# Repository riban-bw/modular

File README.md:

# riban modular

## Overview

Riban modular is an open source and (where practical) open hardware virtual modular synthesiser with physical control panels that fit the Eurorack physical format. See the [wiki](https://github.com/riban-bw/modular/wiki) for documentation.

There are hardware panels that represent each virtual module. The panels are plugged together via a daisy-chain ribbon cable which provides power and a CAN bus for inter-communication. Modules have rotary controls, switches, LEDs, etc. that mimic and control the virtual modules. A Raspberry Pi 5 forms the core, providing the audio processing and interfacing with the hardware panels. Panels are detected automatically when connected, creating a corresponding virtual module within the virtual modular system.

The system consists of a _Brain_ and panels. The Brain consists of a Raspberry Pi 5, STM32F103 microcontroller, CAN connector, audio interface and associated connectors, buttons, pots, etc. Panels consist of STM32F103 microcontroller, CAN connector and buttons, pots, etc.

Each panel is based on a STM32F103C8 microcontroller with a common firmware that supports various quantities and types of controls and indicators. Each panel has a type number that identifies what type of virtual module it represents.

Connect each module to a ribbon cable connector then power up the system. The core will communicate via CAN to detect which panels are installed, assign each panel an id then add a correspoding virtual module to its model.

## Usage

Hardware panels are required to interface with the firmware. See the [wiki](https://github.com/riban-bw/modular/wiki) for documentation.

## Building

There are two core elements to _riban modular_: Hardware panels (including the firmware that runs on them) and the core. Panel firmware is written in C++ for the STMicroelectronics STM32 range of ARM based microcontrollers. The core is written in C++ for the Raspberry Pi ARM based SBC. VSCode IDE is used by the developer with plugins including platformio, which provides the build platform for the STM32 firmware. VSCode is run on a development PC, connected via ssh to the target (Raspberry Pi) platform.

### Core

The core code runs on a Raspberry Pi (4 or later), running [DietPi](https://dietpi.com/) operating system. CMake is used as the build tool. We use some modules from Bogaudio so have a dependancy on their source code with a small patch to exclude the GUI code. To compile the code:

- Install dependencies, e.g. `sudo apt install build-essentials libjack-jackd2-dev git cmake nlohmann-json3-dev`
- Clone this repository, e.g. `git clone --recursive https://github.com/riban-bw/modular.git`
- Change to the directory, e.g. `cd modular/firmware/rmcore`
- Create a build directory, e.g. `mkdir build`
- Change to the build directory, e.g. `cd build`
- Create build files, e.g. `cmake ..`
- Build executable, e.g. `make`

An executable file called _rmcore_ is creaed in the build directory. This may be run with optional command line options, e.g. `rmcore -h` to show help / usage.

### Panels

Each panel has a platformio configuration. These build instructions are for platformio within vscode IDE. (You could just use platformio directly.) I have written up a [guide](https://github.com/riban-bw/blog/wiki/STM32--development-on-PlatformIO-in-VSCode-on-64-bi-ARM) to using platformio within vscode over ssh to a Raspberry Pi to develop STM32 code. Follow that guide to get a working build environment. There are sepearate platformio projects for each panel, defined by a _platformio.ini_ file in the panel's firmware directory.

- Within vscode, click on the platformio icon in the left toolbar.
- Click on "Open Folder" and open the panel directory.
- If this is the first time, platformio will download and install the STM32 toolkit which may take several minutes.
- Click on the tick icon in the bottom toolbar to build the project. First time build may take longer as it builds all the dependant libraries.

To switch panels, use vscode file menu, open folder... Each time a new panel project is opened for the first time, platformio takes some time to configure. (Even on subsequent switches, platformio can take some time to open a project.)

Be aware that rmcore is within the firmware directory but is not a panel firmware and should be built as described in the [above section](#core).

## CAN Protocol

Communication between the Brain and panels uses CAN two wire serial bus. CAN uses differential balanced cabling to provide robust, high speed communication over long distance. Detection of panels uses CAN extended frame format (to allow fewer frames during detection) whilst normal operation uses standad frame format (to allow shorter frames for realtime data). Each panel starts by advertising its 96-bit hardware UID (STM32 serial number). The Brain module detects new panels and negotiates a _panel id_ (1..63) for each. CAN uses a lowest-id-wins mechanism for bus arbitration which allows the Brain to negotiate each panel partaking in the detection process. The panel with the lowest UUID is assigned the next available panel id which then leaves the detection process and joins the pool of configured panels. The Brain iterates over all panels currently advertising their participation in the detection process.

Subsequent communication between the Brain and each panel is via CAN messages initiated by panels for sensor changes (switches, knobs, etc.) or the Brain for indications (LEDs, etc.). The message type is encoded in the CAN ID. Each panel uses CAN filters to only listen for messages from the Brain. Similarly the Brain listens for messages from panels. All CAN traffic occurs between STM32F103 based devices.

#### CAN Message Protocol

CAN message id is 11-bit (std) or 29-bit (ext) word.

Standard CAN format (11-bit id) is used for runtime realtime messages.

Extended CAN format (29-bit id) is used for configuration and firmware update.

#### CAN runtime realtime messages

Brain to panel (B→P) CAN ID: bit [0] = 0, bits [1:7] = panel id (1..63), bits [8:11] = opcode.

Panel to Brain (B←P) CAN ID: bits [0:7] = 0, bits [8:11] = opcode.

Brain to rmcore splits messages into whole bytes, i.e. CAN ID[1], opcode[1], data[8].

rmcore can send messages to the Brain by setting first byte to 0xFF or to a panel by setting first byte to panel (CAN) id.

CAN payload may have varying length (0..8 bytes) depending on message type.

Brain always listens for panel messages and may request values with appropriate commands. This is asynchronous.

Host (RPi) communicates with Brain via serial port, mostly using same CAN protocol, i.e. the Brain passes through the CAN messages. An exception is for panel detection which the Brain handles locally and passes a single message to the host after detecting each panel.

|B↔P| ID       | OpCode | Payload                                   | Purpose|
|---|----------|--------|-------------------------------------------|---------------------------|
|B→P| LED      | 0x01   | Index [0:7] Mode [0:7] RGB1 [0:23] RGB2 [0:23]   | Set LED type and mode. RGB colours are both optional |
|B←P| ADC      | 0x02   | PanelId [0:7] Index [0:7] Value [0:15]           | ADC value|
|B←P| SW       | 0x03   | PanelId [0:7] Index[0:7] EventType [0:7]         | See below for event types |
|B←P| ENC      | 0x04   | PanelId [0:7] Index [0:7] Value [0:7]            | Encoder value +/- |
|B←P| PNL_DUMP | 0xF1   | PanelId [0:7]                                    | Request panel to send its parameter values |
|B←P| ALIVE    | 0x0E   |                                                  | Sent periodically if no other data sent to support watchdog |
|B→P| RESET    | 0x0F   |                                                  | Request panel to reset to detection mode |
|B←H| NUM_PNL  | 0x01   |                                                  | Request quantity of detected panels
|B←H| PNL_INFO | 0x01   |                                                  | Request type of all panels
|B→H| PNL_INFO | 0x01   | PanelId [0:5] Type [0:31] UUID [0:95] Ver [0:31] | Panel type (sent when new panel detected or PNL_INFO requested)
|B→H| PNL_REMOVED | 0x02 | PanelId [0:5] UUID [0:95]                       |
|B←H| PNL_RUN  | 0x03 |                                                    | Request all panels go to run mode

##### LED Modes
|Value|Mode|
|---|---|
|0x00|Off|
|0x01|Colour 1 on|
|0x02|Colour 2 on|
|0x03|Flash colour 1 / colour 2|
|0x04|Fast flash colour 1 / colour 2|
|0x05|Pulse colour 1 / colour 2|
|0x06|Fast pulse colour 1 / colour 2|

##### Switch States
|Value|State|
|---|---|
|0x00|Release|Sent when a button is released less than 0.5s after it was pressed (short press) or after a long press has triggered|
|0x01|Press|Always sent when a button is pressed|
|0x02|Bold|Sent when a button is released more than 0.5s after it was pressed but a long press has not triggered|
|0x03|Long|Sent when a button is held for longer than 1.5s|

#### Panel Detection

Panels advertise themselves with a CAN message which the Brain detects and starts a negotation. Detection messages use extended CAN ID which is 29-bits long (compared with standard frames used for realtime messages which are 11-bits). Each panel advertises itself by encoding its 96-bit UUID in the CAN ID of 4 consecutive messages. Each message is acknowledged by the Brain, indicating which panel UUID are accepted. Only panels that match that segment of the UUID continue with the negotiation. Eventually only one panel remains and is assigned a panel ID. Finally the panel indicates it has accepted the panel, sending its type and version. This allows the Brain to build a table of panel UUID, panel ID and panel type so that the core can create the appropriate virtual modules. It also allows the Brain to know whether a panel is running old firmware, allowing firmware update. The table is used to ensure that existing panels that restart, e.g. after a firmware update get the same panel ID.

|B⬌P| ID        | ID                | Payload                    | Purpose |
|----|-----------|-------------------|----------------------------|---------------------------|
|B←P| DETECT_1  | 0x1F<UUID[0:23]>  |                            | Notify Brain that panel is added to bus but not initialised |
|B→P| DETECT_1  | 0x1F000000        | UUID[0:23]                 | Brain acknowledges lowest UUID panels |
|B←P| DETECT_2  | 0x1E<UUID[24:47]> |                            | Panel requests detect stage 2 |
|B→P| DETECT_2  | 0x1E000000        | UUID[24:47]                | Brain acknowledges lowest UUID panels |
|B←P| DETECT_3  | 0x1D<UUID[48:71]> |                            | Panel requests detect stage 3 |
|B→P| DETECT_3  | 0x1D000000        | UUID[48:71]                | Brain acknowledges lowest UUID panels |
|B←P| DETECT_4  | 0x1C<UUID[71:95]> |                            | Panel requests detect stage 4 |
|B→P| DETECT_4  | 0x1C000000        | UUID[72:95] PanelID[0:7]   | Brain acknowledges UUID of only remaining panel |
|B←P| ACK_ID    | 0x1B0000<PanelId> | Type [0:31] Version [0:31] | Panel acknowledges ID and informs Brain of its version & type |

#### Broadcast messages and firmware update

The CAN ID 0x000 is used to broadcast messages to all panels. This is the highest priority CAN ID (lowest value wins all bus conflict negotiation) and is used for low latency messaging (e.g. synchronisation) and firmware update. The first byte of a broadcast payload data is the opcode for a command. All broadcast messages use standard (11-bit) CAN format.

Broadcast messages
|Dir | ID        | ID         | Payload                           | Purpose
|----|-----------|------------|-----------------------------------|---------------------------------------------------------
|B→P| BROADCAST | 0x00000000 | OPCODE[0:7]                       | Broadcast from Brain payload contains opcode (see below) |
|B→P| BROADCAST | 0x00000000 | 0x01 UUID[0:23]                   | Start detection - all panels should join detection without software reset |
|B→P| BROADCAST | 0x00000000 | 0x02 PanelType [0:23] Ver [0:31]  | Start firmware update |
|B→P| BROADCAST | 0x00000000 | 0x03 Checksum [0:31]              | End firmware update |
|B→P| FIRMWARE  | 0x01000000 | Firmware Block [0:63]             | Firmware update data block |
|B→P| BROADCAST | 0x00000000 | 0xFF                              | Full reset - all panels should perform software reset |

Firmware is started with the broadcast message (CAN ID=0x000) with opcode 0x02. The panel type and firmware version are sent in this message. Any panel of this type with an older firmware will join the firmware update. Subsequent firmware update messages use the CAN ID 0x400 (msb set) with 8 bytes of firmware data. Panels configure a CAN filter to listen to this address during firmware update only. Upon completion of firmware update the Brain sends broadcast message with opcode 0x03 and a 32-bit checksum of the firmware data. The Brain ends its firmware update. Panels validate the checksum then apply the new firmware, restart and advertise as new panels.

#### Watchdog

Each panel periodically sends an ALIVE message if no other message has been sent in the previous 1.5s. If the Brain has not received any message from a panel for longer than 2s it assumes the panel has been removed  from the bus and removes its entry from the panel table. This triggers removal of the corresponding virtual module.

## Configuration

Configuration is stored in config.json which is loaded before command line parameters are parsed, so command line parameters take precedent.

Global settings are defined in the "global" object.

```
{
    "global": { # Global settings
        "polyphony": 1 # Quantity of concurrent voices (1..16)
    }
}
```

Each panel is defined in "panel" object.

```
{
    "panels" : { # Object of panel types
        "1": { # Object of panel configuration indexed by panel type id
            "module": "vco", # Name of the module type this panel controls
            "buttons": [ # List of buttons, indexed by physical button number
                [0, # Button function (input, poly input, output, poly output, param)
                0], # Index of the parameter or input/output
                # .. more button configs
            ],
            "leds": [ # List of LEDs, indexed by physical LED number
                [0, # LED function  (input, poly input, output, poly output, param)
                0], # Index of parameter or input/output
                # ... more LEDs
            ],
            "adcs": [ # List of parameters, indexed by physical ADC number
                0, # Parameter index
                # ... more ADCs
            ]
            "encs": { # List of parameters, indexed by physical PEC11 encoder number
                0, # Parameter index
                # ... more encoders
            }
        }, # ... More panel types
    }
}
```

panel_types.h defines mapping of panel types to module types and defines the STM32F103 pins used for sensors (controls) on each panel. 

## License

_riban modular_ is free and open source software, avaialble for distibution, use and modification by all. It has three open source licences, each applied to different parts of the code. Each source code file (including headers) contain a copyright notice describing which license applies to that part of the code. If a file is missing this banner, LGPL v3 is applied.

### LGPL V3
LGPL v3 is used for the core software and some plugins. This protects the core application whilst allowing non-open source plugins to be hosted by exercising dynamic linking with runtime loading (plugin exception). The text of the LGPL v3 license is distributed with the source code within the file called, lgpl-3.0.txt and may also be obtained from https://www.gnu.org/licenses/lgpl-3.0.en.html.

### GPL V3
To support plugins derived from GPL licensed code, some plugins have been licenced using GPL v3. These plugins continue to be fully copy-left protected whilst also able to be loaded into the core application using dynamic linking with runtime loading (plugin exception). The text of the GPL v3 license is distributed with the source code within the file called, gpl-3.0.txt and may also be obtained from https://www.gnu.org/licenses/gpl-3.0.en.html.

### MIT
To encourage third party plugin developement, there is a plugin template released under MIT license. This permits the use of the template as the basis of new plugins with the option for the author to release the derived work under any other license. We encourage use of LGPL for plugins where an open source license is required or preferred.

### Guidance and advice for plugin creators

If you are creating plugins to run within _riban modular_, you may use the `template.h` and `template.cpp` files as the boiler plate code. These files are published under the MIT license, specifically to allow and encourage developers to create new plugins without restricitve licensing constraints. You may create a new plugin and use the _riban modular_ cmake based build system to create the shared library. You may release this under a license that best suits your use case. You must attribute riban ltd as the author of the original template code, as described in the template source code.

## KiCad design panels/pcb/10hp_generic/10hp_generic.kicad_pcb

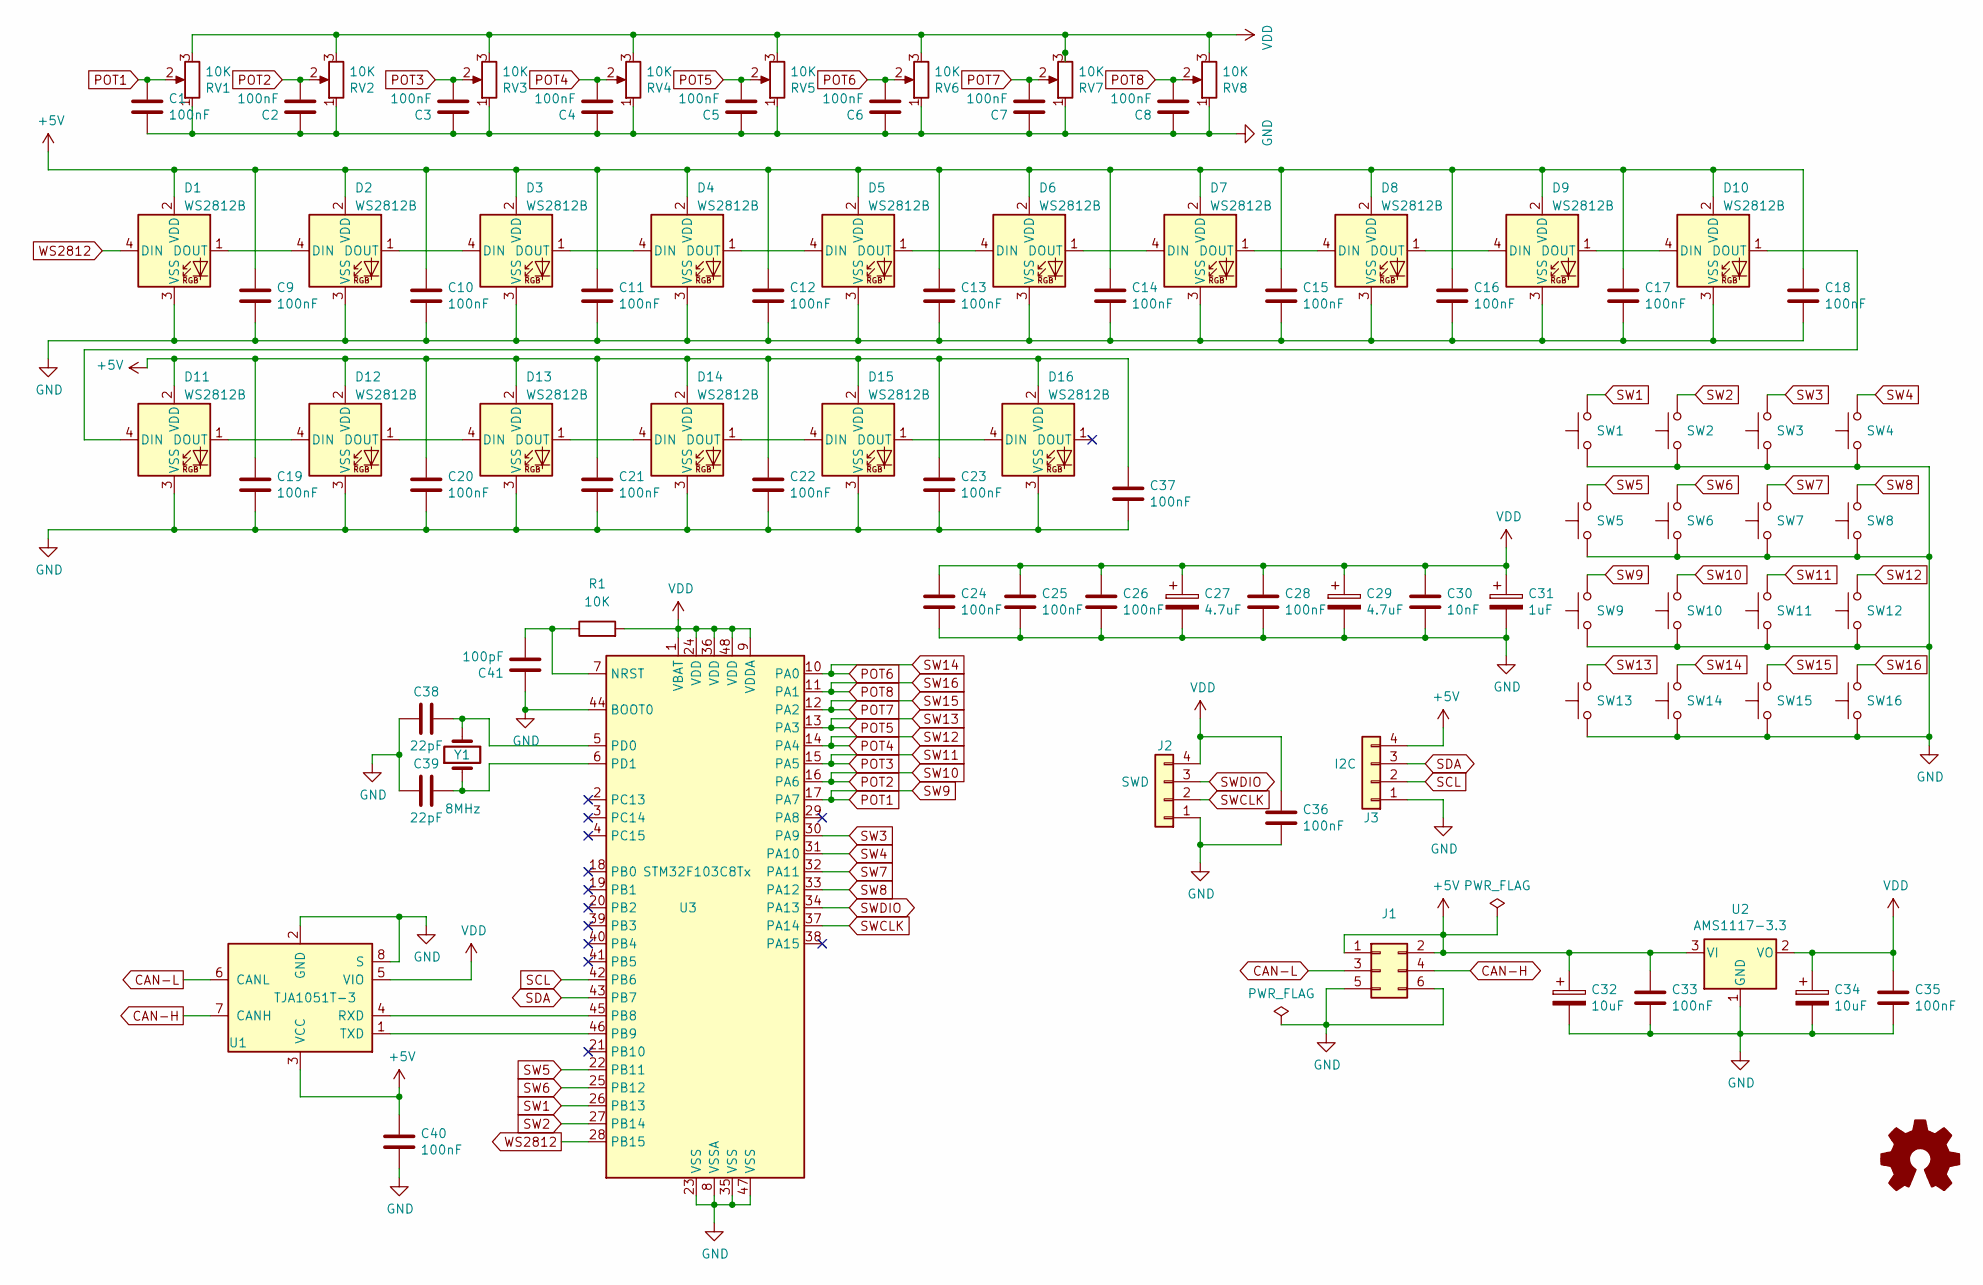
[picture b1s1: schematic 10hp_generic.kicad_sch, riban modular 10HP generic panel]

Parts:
C1, C2, C3, C4, C5, C6, C7, C8, C9, C10, C11, C12, C13, C14, C15, C16, C17, C18, C19, C20, C21, C22, C24, C25, C26, C28, C33, C35, C36, C40: 100nF; C_0402_1005Metric; LCSC C1525
C23, C37: 100nF; C_0603_1608Metric; LCSC C14663
C27, C29: 4.7uF; C_0805_2012Metric; LCSC C1779
C30: 10nF; C_0402_1005Metric; LCSC C15195
C31: 1uF; C_0402_1005Metric; LCSC C52923
C32, C34: 10uF; C_0805_2012Metric; LCSC C15850
C38, C39: 22pF; C_0603_1608Metric; LCSC C326840
C41: 100pF; C_0402_1005Metric; LCSC C1546
D1, D2, D3, D4, D5, D6, D7, D8, D9, D10, D11, D12, D13, D14, D15, D16: WS2812B; LED_XL-1615RGBC-WS2812B; LCSC C5349954
J1: CAN_PWR; IDC-Header_2x03_P2.54mm_Vertical
J2: SWD; PinHeader_1x04_P2.54mm_Vertical
J3: I2C; PinHeader_1x04_P2.54mm_Vertical
R1: 10K; R_0402_1005Metric
RV1, RV2, RV3, RV4, RV5, RV6, RV7, RV8: 10K; Potentiometer_9mm_Vertical; LCSC C470336
SW1, SW2, SW3, SW4, SW5, SW6, SW7, SW8, SW9, SW10, SW11, SW12, SW13, SW14, SW15, SW16: SW_Push; SW_PUSH_6mm_H4.3mm; LCSC C5260475
U1: TJA1051T-3; SOIC-8_3.9x4.9mm_P1.27mm; LCSC C38695
U2: AMS1117-3.3; SOT-223; LCSC C6186
U3: STM32F103C8Tx; LQFP-48_7x7mm_P0.5mm; LCSC C8734
Y1: 8MHz; HC-49S; LCSC C12674

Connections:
+5V: C9.1, C10.1, C11.1, C12.1, C13.1, C14.1, C15.1, C16.1, C17.1, C18.1, C19.1, C20.1, C21.1, C22.1, C23.1, C32.1, C33.1, C37.1, C40.1, D1.2 (VDD), D2.2 (VDD), D3.2 (VDD), D4.2 (VDD), D5.2 (VDD), D6.2 (VDD), D7.2 (VDD), D8.2 (VDD), D9.2 (VDD), D10.2 (VDD), D11.2 (VDD), D12.2 (VDD), D13.2 (VDD), D14.2 (VDD), D15.2 (VDD), D16.2 (VDD), J1.1, J1.2, J3.4, U1.3 (VCC), U2.3 (VI)
CAN-H: J1.4, U1.7 (CANH)
CAN-L: J1.3, U1.6 (CANL)
GND: C1.2, C2.1, C3.1, C4.1, C5.1, C6.1, C7.1, C8.1, C9.2, C10.2, C11.2, C12.2, C13.2, C14.2, C15.2, C16.2, C17.2, C18.2, C19.2, C20.2, C21.2, C22.2, C23.2, C24.2, C25.2, C26.2, C27.2, C28.2, C29.2, C30.2, C31.2, C32.2, C33.2, C34.2, C35.2, C36.2, C37.2, C38.1, C39.1, C40.2, C41.1, D1.3 (VSS), D2.3 (VSS), D3.3 (VSS), D4.3 (VSS), D5.3 (VSS), D6.3 (VSS), D7.3 (VSS), D8.3 (VSS), D9.3 (VSS), D10.3 (VSS), D11.3 (VSS), D12.3 (VSS), D13.3 (VSS), D14.3 (VSS), D15.3 (VSS), D16.3 (VSS), J1.5, J1.6, J2.1, J3.1, RV1.1, RV2.1, RV3.1, RV4.1, RV5.1, RV6.1, RV7.1, RV8.1, SW1.1, SW2.1, SW3.1, SW4.1, SW5.1, SW6.1, SW7.1, SW8.1, SW9.1, SW10.1, SW11.1, SW12.1, SW13.1, SW14.1, SW15.1, SW16.1, U1.2 (GND), U1.8 (S), U2.1 (GND), U3.8 (VSSA), U3.23 (VSS), U3.35 (VSS), U3.44 (BOOT0), U3.47 (VSS)
unnamed: D1.1 (DOUT), D2.4 (DIN)
unnamed: D2.1 (DOUT), D3.4 (DIN)
unnamed: D3.1 (DOUT), D4.4 (DIN)
unnamed: D4.1 (DOUT), D5.4 (DIN)
unnamed: D5.1 (DOUT), D6.4 (DIN)
unnamed: D6.1 (DOUT), D7.4 (DIN)
unnamed: D7.1 (DOUT), D8.4 (DIN)
unnamed: D8.1 (DOUT), D9.4 (DIN)
unnamed: D9.1 (DOUT), D10.4 (DIN)
unnamed: D10.1 (DOUT), D11.4 (DIN)
unnamed: D11.1 (DOUT), D12.4 (DIN)
unnamed: D12.1 (DOUT), D13.4 (DIN)
unnamed: D13.1 (DOUT), D14.4 (DIN)
unnamed: D14.1 (DOUT), D15.4 (DIN)
unnamed: D15.1 (DOUT), D16.4 (DIN)
unnamed: U1.4 (RXD), U3.45 (PB8)
unnamed: U1.1 (TXD), U3.46 (PB9)
unnamed: C41.2, R1.1, U3.7 (NRST)
unnamed: C38.2, U3.5 (PD0), Y1.2
unnamed: C39.2, U3.6 (PD1), Y1.1
POT1: C1.1, RV1.2, SW9.2, U3.17 (PA7)
POT2: C2.2, RV2.2, SW10.2, U3.16 (PA6)
POT3: C3.2, RV3.2, SW11.2, U3.15 (PA5)
POT4: C4.2, RV4.2, SW12.2, U3.14 (PA4)
POT5: C5.2, RV5.2, SW13.2, U3.13 (PA3)
POT6: C6.2, RV6.2, SW14.2, U3.10 (PA0)
POT7: C7.2, RV7.2, SW15.2, U3.12 (PA2)
POT8: C8.2, RV8.2, SW16.2, U3.11 (PA1)
SCL: J3.2, U3.42 (PB6)
SDA: J3.3, U3.43 (PB7)
SW1: SW1.2, U3.26 (PB13)
SW2: SW2.2, U3.27 (PB14)
SW3: SW3.2, U3.30 (PA9)
SW4: SW4.2, U3.31 (PA10)
SW5: SW5.2, U3.22 (PB11)
SW6: SW6.2, U3.25 (PB12)
SW7: SW7.2, U3.32 (PA11)
SW8: SW8.2, U3.33 (PA12)
SWCLK: J2.2, U3.37 (PA14)
SWDIO: J2.3, U3.34 (PA13)
VDD: C24.1, C25.1, C26.1, C27.1, C28.1, C29.1, C30.1, C31.1, C34.1, C35.1, C36.1, J2.4, R1.2, RV1.3, RV2.3, RV3.3, RV4.3, RV5.3, RV6.3, RV7.3, RV8.3, U1.5 (VIO), U2.2 (VO), U3.1 (VBAT), U3.9 (VDDA), U3.24 (VDD), U3.36 (VDD), U3.48 (VDD)
WS2812: D1.4 (DIN), U3.28 (PB15)

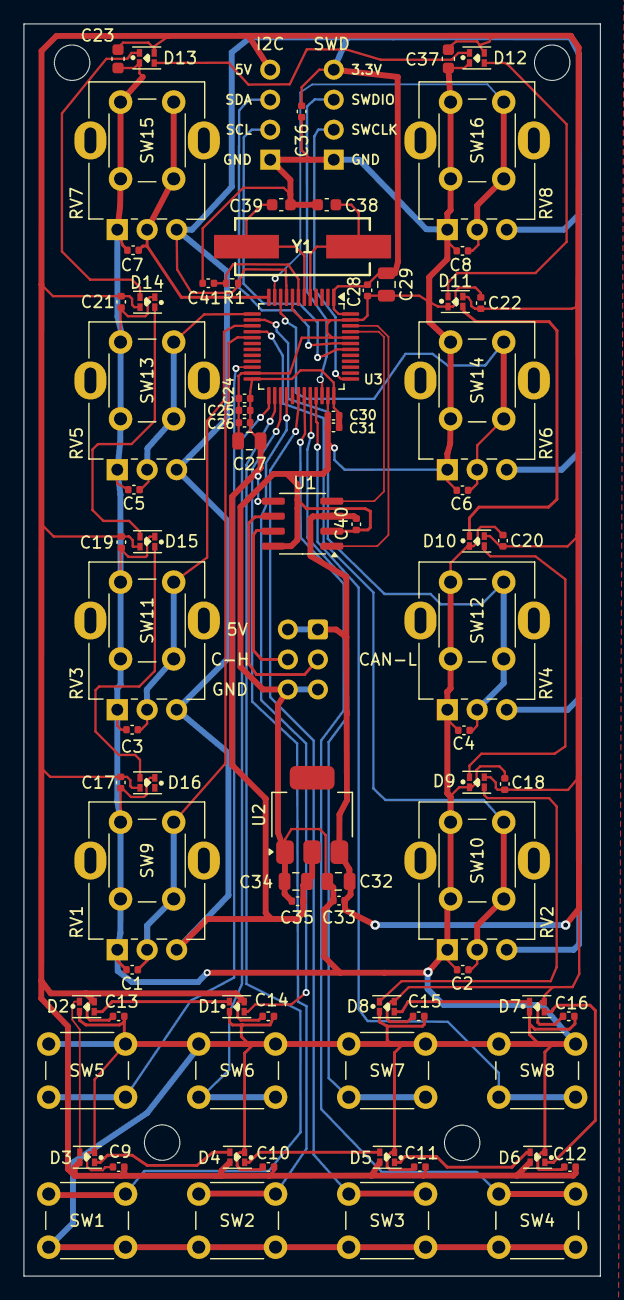
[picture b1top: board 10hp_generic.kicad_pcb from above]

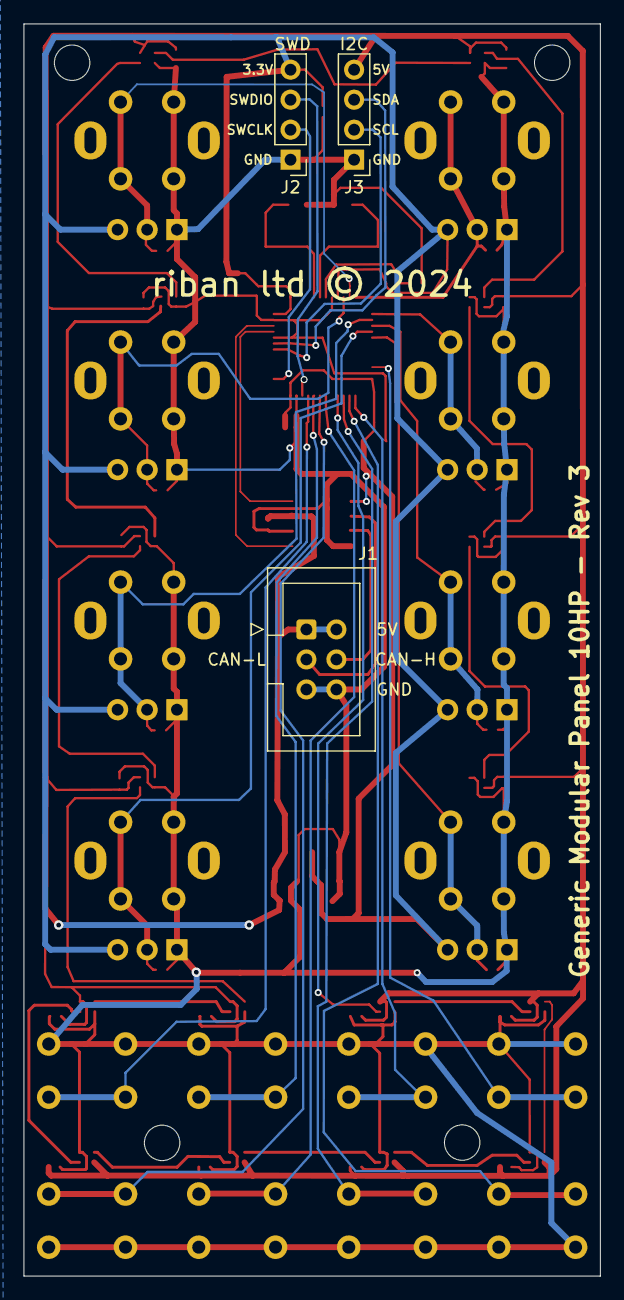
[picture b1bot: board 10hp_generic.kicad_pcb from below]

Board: 2 copper layers, 48.8 x 106.0 mm, 89 parts (3 on the bottom side), 46 nets.

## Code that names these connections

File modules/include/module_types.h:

/* riban modular
  
  Copyright 2023 riban ltd <info@riban.co.uk>

  This file is part of riban modular.
  riban modular is free software: you can redistribute it and/or modify it under the terms of the GNU General Public License as published by the Free Software Foundation, either version 3 of the License, or (at your option) any later version.
  riban modular is distributed in the hope that it will be useful, but WITHOUT ANY WARRANTY; without even the implied warranty of MERCHANTABILITY or FITNESS FOR A PARTICULAR PURPOSE. See the GNU General Public License for more details.
  You should have received a copy of the GNU General Public License along with riban modular. If not, see <https://www.gnu.org/licenses/>.

  Defines each module configuration based on preprocessor directive MODULE_TYPE which should be defined in build system.
*/

#ifndef MODULE_TYPE
#error Module type not defined
#endif //MODULE_TYPE

/* Available GPI (STM32F103 Bluepill dev board)
PORT|ADC|PWM|COMMS|Note
-----------------------
PA0 | X | X |     |
PA1 | X | X |     |
PA2 | X | X |     |
PA3 | X | X |     |
PA4 | X |   |     |
PA5 | X |   |     |
PA6 | X | X |     |
PA7 | X | X |     |
PA8 |   | X |     |
PA9 |   | X |     |
PA10|   | X |     |
PA11|   |   |USB- |Only for debug
PA12|   |   |USB+ |Only for debug
PA13|   |   |     |End header programming pin
PA14|   |   |     |End header programming pin
PA15|   |   |     |
PB0 | X | X |     |
PB1 | X | X |     |
PB2 |   |   |     |Top header boot pin
PB3 |   |   |     |
PB4 |   |   |     |
PB5 |   |   |     |
PB6 |   | X |     |
PB7 |   | X |     |
PB8 |   | X |     |
PB9 |   | X |     |
PB10|   |   |SCL  |I2C
PB11|   |   |SDA  |I2C
PB12|   |   |     |
PB13|   |   |     |
PB14|   |   |     |
PB15|   |   |MOSI2|WS2812 control
PC13|   |   |LED  |
PC14|   |   |     |Next module reset
PC15|   |   |     |
*/

#define ADC_PINS {PA0, PA1, PA2, PA3, PA4, PA5, PA6, PA7, PB0, PB1}
#define PWM_PINS {PA0, PA1, PA2, PA3, PA6, PA7, PA8, PA9, PA10, PB0, PB1, PB6, PB7, PB8, PB9}
#define GPI_PINS {PB0, PB1, PB3, PB4, PB5, PB6, PB7, PB8, PB9, PB12, PB13, PB14, PC15, PA15}
#define SCL_PIN PB10
#define SDA_PIN PB11
#define MOSI_PIN PB15 //WS2812 LED data
#define RESET_PIN PC14

#if MODULE_TYPE==1
// Host Audio
//!@todo May want a core module that provides audio & MIDI
#define ADCS 1
#define SWITCHES 4
#define WSLEDS 4
#endif // MODULE_TYPE 1

#if MODULE_TYPE==11
// VCV Fundamental VCO
#define ADCS 4
#define SWITCHES 10
#define WSLEDS 10
#endif // MODULE_TYPE 11

#if MODULE_TYPE==12
// VCV Fundamental VCF
#define ADCS 6
#define SWITCHES 6
#define WSLEDS 6
#endif // MODULE_TYPE 12

#if MODULE_TYPE==13
// VCV Fundamental VCA
#define ADCS 1
#define SWITCHES 3
#define WSLEDS 3
//!@todo Indicate level, e.g. +24 (WS)LEDs
#endif // MODULE_TYPE 13

#if MODULE_TYPE==14
// VCV Fundamental ADSR
#define ADCS 8
#define SWITCHES 8
#define WSLEDS 8
#endif // MODULE_TYPE 14

#if MODULE_TYPE==15
// VCV Fundamental VCA-2
#define ADCS 2
#define SWITCHES 8
#define WSLEDS 8
#endif // MODULE_TYPE 15

#if MODULE_TYPE==16
// VCV Fundamental VCA MIX
#define ADCS 10
#define SWITCHES 14
#define WSLEDS 14
#endif // MODULE_TYPE 16

#if MODULE_TYPE==17
// VCV Fundamental MERGE
#define ADCS 0
#define SWITCHES 17
#define WSLEDS 17
#endif // MODULE_TYPE 17

#if MODULE_TYPE==18
// VCV Fundamental RANDOM
#define ADCS 8
#define SWITCHES 12
#define WSLEDS 12
#endif // MODULE_TYPE 18

#if MODULE_TYPE==19
// VCV Fundamental NOIZ
#define ADCS 0
#define SWITCHES 7
#define WSLEDS 7
#endif // MODULE_TYPE 19

#if MODULE_TYPE==20
// VCV Fundamental M/S
#define ADCS 2
#define SWITCHES 10
#define WSLEDS 10
#endif // MODULE_TYPE 20

#if MODULE_TYPE==21
// VCV Fundamental SPLIT
#define ADCS 0
#define SWITCHES 17
#define WSLEDS 17
#endif // MODULE_TYPE 21

#if MODULE_TYPE==22
// VCV Fundamental 4-1
#define ADCS 0
#define SWITCHES 7
#define WSLEDS 7
#define LEDS 3
#endif // MODULE_TYPE 22

#if MODULE_TYPE==23
// VCV Fundamental 1-4
#define ADCS 0
#define SWITCHES 7
#define WSLEDS 7
#define LEDS 3
#endif // MODULE_TYPE 23

#if MODULE_TYPE==24
// VCV Fundamental SEQ3
#define ADCS 28
#define SWITCHES 31
#define WSLEDS 31
#endif // MODULE_TYPE 24

#if MODULE_TYPE==25
// VCV Fundamental PULSES
#define ADCS 0
#define SWITCHES 30
#define WSLEDS 30
#endif // MODULE_TYPE 25

#if MODULE_TYPE==26
// VCV Fundamental MUTES
#define ADCS 0
#define SWITCHES 30
#define WSLEDS 30
#endif // MODULE_TYPE 26

#if MODULE_TYPE==27
// VCV Fundamental 8VERT
#define ADCS 8
#define SWITCHES 16
#define WSLEDS 16
#endif // MODULE_TYPE 27

#if MODULE_TYPE==28
// VCV Fundamental MIX
#define ADCS 1
#define SWITCHES 7
#define WSLEDS 7
#endif // MODULE_TYPE 28

#if MODULE_TYPE==29
// VCV Fundamental LFO
#define ADCS 4
#define SWITCHES 10
#define WSLEDS 10
#endif // MODULE_TYPE 29

#if MODULE_TYPE==30
// VCV Fundamental OCT
#define ADCS 1
#define SWITCHES 3
#define WSLEDS 3
#endif // MODULE_TYPE 30

#if MODULE_TYPE==31
// VCV Fundamental WT VCO
#define ADCS 4
#define SWITCHES 7
#define WSLEDS 7
//!@todo Load, select and indicate wavetable / waveform
#define DISPLAY 1
#endif // MODULE_TYPE 31

#if MODULE_TYPE==32
// VCV Fundamental SUM
#define ADCS 1
#define SWITCHES 2
#define WSLEDS 2
#define LEDS 6
#endif // MODULE_TYPE 32

#if MODULE_TYPE==33
// VCV Fundamental QNT
#define ADCS 1
#define SWITCHES 14
#define WSLEDS 14
//!@todo Implement keyboard
#endif // MODULE_TYPE 33

#if MODULE_TYPE==34
// VCV Fundamental WT LFO
#define ADCS 4
#define SWITCHES 7
#define WSLEDS 7
//!@todo Load, select and indicate wavetable / waveform
#endif // MODULE_TYPE 33

#if MODULE_TYPE==35
// VCV Fundamental DELAY
#define ADCS 8
#define SWITCHES 8
#define WSLEDS 8
#endif // MODULE_TYPE 35

/*===========================================================================
    Define macros not specified (used) by module

    DO NOT CHANGE THIS - add new modules above
*/

#ifndef SWITCHES
#define SWITCHES 0 // Defines quantity of switch pins
#endif //SWITCHES
#ifndef ADCS
#define ADCS 0 // Defines quantity of analogue inputs like potentiometers
#endif //ADCS
#ifndef LEDS
#define LEDS 0 // Defines quanity of simple LED outputs
#endif //LEDS
#ifndef WSLEDS
#define WSLEDS 0  // Defines quantity of WS2812 LEDs
#endif //WSLEDS

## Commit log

2023-04-03 Adds module firmware source
2023-04-05 Adds Python host
2023-04-05 Port code to PlatformIO/VSCode
2023-08-05 Adds OSC interface to Cardinal
2023-08-07 Adds OSC interface to (riban modified) Cardinal. Updates README.
2023-08-07 Fix typo in README
2023-08-13 Implement I2C interface. Add module configuration. Add WS2812 LED control.
2023-08-13 Fixes I2C issues
2023-08-14 Add I2C command to turn LED on with colour 2
2023-08-14 Add ability to change LED colour and mode separately
2023-08-20 Add config for VCV modules. Reallocate GPI pins. Add function to temporarily turn all LEDs off. Synchronise pulse and flash across module (still need to sync between modules). Fast pulse LEDs on rese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
2023-08-22 Add function to get changed value from module. Use 16-bit values instead of 32-bit. Include address of data in return message. Reduce I2C responses from 4 to 3 bytes. Add more info to serial debug in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
2023-08-22 Fix setting i2c address
2023-08-25 Started integration with rack
2023-08-26 Initial version of host code (modular.py)
2023-08-27 Use min/max for rack parameter scaling / offset. Implement routing logic including LED feedback. Reduce panel reset LED flash duration.
2023-09-01 Do not use reset - use run GPI
2023-09-01 Add 10HP PCB
2023-09-08 PCB for generic 10hp panel (r1) including front panel for bogaudio VCO
2023-09-08 Fixes PCB footprint for C27 & C29
2023-09-08 Fixes some component values
2023-09-09 R2 of generic PCB using different components
2023-09-15 Add 1-wire module detection
2023-09-16 Adds brain front panel
2023-09-28 Fix host comms.
2023-09-28 Fixes and ehancements
2023-09-28 Adds VCF module. Connect jack audio at startup.
2023-09-28 Add Bogaudio LVCF
2023-10-02 Adds universal panel
2023-10-06 Refactor to use module id instead of I2C address - wip!
2023-10-09 Initial attempt at adding a website to gitlab pages
2023-10-09 Add website builder script
2023-10-09 Try to make website builder script work
2023-10-09 More website stuff
2023-10-13 Improvements to generic 10HP board layout. Implement exponential moving average filter on ADC reads.
2023-10-13 Fixes VCO PWM/FM input swap. Fixes errors in refactor of multiple module hosting panels.
2023-11-06 Typo in panel.cpp
2023-11-11 Adds STM32F1 generic panel firmware using CAN bus - wip
2023-11-11 Fix panel type not being set
2023-12-22 Changes made on laptop that needs to be wiped
2024-02-01 Add CAN based firmware
2024-02-01 Implement WS2812 LED control
2024-02-01 Adjust LED flash/pulse rates
2024-02-01 Rationalise CAN messaging. Add switches.
2024-02-02 Use 10kbps CAN for testing - avoid unreliable CAN interferring with tests. Handle existing panels resetting / connecting to brain. (Reuse existing records.) Implement I2C to CAN message sending. Fix 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
2024-02-06 Fixes CAN based detection
2024-02-06 Adds ADC and python test script
2024-02-06 Tuning EMA filter
2024-02-26 Rev 3 Firmware
    Replace I2C interface with CAN.
    Change from STM32F0 to STM32F1 processor.
    Panel detection now done on CAN so can remove 2 detect wires.
2024-02-26 Adds 10HP Generic PCB
2024-02-26 Adds front panels
2024-02-29 PCB design for generic r3 (wip)
2024-03-05 Rev 3 PCB routing done
2024-03-07 Rev 3 boards complete - probably
2024-03-08 R3 PCB and front panel
2024-03-14 Adds boilerplate for core host application
2024-04-05 Updated PCB fixing issues with r3: Reversed power pins on U1. Increase size of potentiometer anchors holes. Enable external high speed clock. Enable all LEDs, switches and pots.
2024-04-05 Fixes for firmware
2024-04-08 Replace I2C with USART
2024-04-09 Create brain STM32F103 firmware
2024-04-10 Implementing USART interface in host application - wip
2024-04-10 1Mbps usart mostly working
2024-04-11 Some optimisation and removal of stale code
2024-04-11 Fixes to generic 10hp schematic and PCB
2024-04-11 Tidy files
2024-04-11 Removes pages publish script (no longer using for webpage)
2024-09-23 Adds initial core code
2024-09-23 Work on core
2024-09-23 Add version and start of rack stub
2025-04-24 Adds oscillator.
2025-04-24 Remove oscillator code from main. Use static header file for wavetable data. Add application to build wavetable data. Add square wave oscillator with PWM. Add code documentation. Fix copyright notice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
2025-04-25 Switch from alsa to jack. Implement plugin mechanism for modules.
2025-04-25 Improve and simplify configuration of plugins. Add one-pole filtering of oscillator frequency control to reduce zipping.
2025-04-25 Adds amplifer module
2025-04-26 Move info into module constructor
2025-04-26 Add MIDI. Add filter (not working properly yet). Use CV input to oscillator to set frequency based on 1v/oct. Fix segfault when setting param value.
2025-04-27 Add polyphony (max 16, set by command line parameter -p)
2025-04-28 Use jack samplerate. Implement envelope. Implement polyphony. Add oscillator waveform morph control.
2025-04-28 Adds MIDI pitch bend. Adds MIDI CC. Save and restore routing.
2025-04-28 Add base MIDI CC parameter. Add VCO waveform morph CV input. Fix envelope decay parameter. Fix square wave pulse width. Add xrun monitor. Fix polyphony setting. Remove debug.
2025-04-28 Adds noise generator module
2025-04-28 Adds VCF
2025-04-29 Add panel using UUID. Jack client name now includes UUID in hex. Remove noise from wavetable. Use 1Hz period for wavetable. Improve LPF code. Disconnect from jack on close.
2025-04-29 Updated CMake to auto build wavetable. Change Node class to Module. Fix exception with jack callbacks when closing. Add extra filter types: LP, HP, BP, etc. Provide error, info, debug helper function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
2025-04-29 Small doc typo
2025-04-29 Adds 4 channel mixer module
2025-04-29 Adds random (SH) module
2025-04-29 Adds 8-step sequencer
2025-05-01 Update LICENSE to LGPL3
    To facilitate linking to variously licensed plugins, the core application will use LGPL version 3.
2025-05-01 Use dynamically linked libs for plugin modules
2025-05-01 Renamed modules
2025-05-01 Use macro to define create module function. Change class names, e.g. VCA.
2025-05-01 Add console output routines to plugins
2025-05-01 Update each module when polyphony changes
2025-05-01 Fixes switching polyphony
2025-05-02 Add CLI.
2025-05-03 Store module parameters in snapshot file
2025-05-05 Adds description to each module to facilitate accessibility. Use shared lib name for module name instead of explicitly defining in info. Rename modules to fit shared lib naming. Use configuration fil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
2025-05-06 Use config.json for configuration. Implement panel configuration.
2025-05-06 Add LED check. Create config directories if missing. Fix addPanel.
2025-05-07 Update CAN & USART comms protocol. Fix LED control. Implement better mapping of hardware panels to software modules.
2025-05-07 Change source file name
2025-05-07 Simplify setLed functions
2025-05-07 Fixes snapshots not making all connections if run with different polyphony.
2025-05-07 Remove unused functions
2025-05-07 Add rmcore engineering doc
2025-05-09 Remove stale modules when panel messages timeout. Implement rmcore control of panels, e.g. setting run mode. Fix segfault in vco. Fix missing parameters in vco. Only register jack connect callback in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
2025-05-09 Remove .p (add panel) from CLI. (Panels need keep alive CAN messages). Fix typos. Resolve some todos.
2025-05-10 Use json for snapshots
2025-05-10 Update doc
2025-05-11 Change rmcore state to use arrays rather than objects. Fix debug output not being enabled early enough. Add try/catch around json access. Fix polyphony being set incorrectly by config. Handle jack se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
2025-05-12 Update README.md
    Adds nlohmann-json3-dev dependancy.
2025-05-13 Fixes polyphonic mode by removing loading polyphony from snapshot. Module may have any quantity of MIDI inputs and outputs defined. Rationalise port names to use "output" or "input" and not "out" or 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
2025-05-13 Add serial port command line option
2025-05-15 Add ability to use Bogaudio plugins. Add slew limiter and vcf plugin.
2025-05-15 Use riban_modular branch of Bogaudio
2025-05-15 Fixes build
2025-05-15 Add individual CV range parameter for each MIDI CC (1V, 10V, +/-5V), Fix VCF output. Adds Bogaudio noise generator. Update docs.
2025-05-15 Removed debug
2025-05-15 Add Bogaudio ring and amplitude modulator
2025-05-15 Adds attribution and copyright notices for Bogaudio derived classes.
2025-05-15 Change licence statement in Bogaudio plugins to match GPL3 licence the upstream plugin uses. These plugins can be licenced as GPL3 and uses with dynamic linking with runtime loading / plugin exceptio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
2025-05-16 License clarification
2025-05-16 Further license clarification
2025-05-16 Fix VCF (using wrong in/outs). Optimise some plugins. (Do not check for connection on every frame.)
2025-05-16 Optmise bogvcf
2025-05-16 Remove config and version files
2025-05-16 Fix MIDI CC name
2025-05-16 Set vcf default param vals
2025-05-17 Add fine and coarse controls to VCO. Use normalised parameter range for VCO frequency.
2025-05-18 Adds Bogaudio VCO
2025-05-18 Range check Bogaudio VCO parameters should avoid exception. Optimise jack connection detection.
2025-05-18 Add discrete octave steps parameter to bogvco
2025-05-18 Add delay and hold phases to envelope generator. Add linear, log & exponential curves to attack, decay and release phases. Add LED setMode function. Catch exceptions in CLI.
2025-05-19 Adds ladder filter. Some optimisation of Bogaudio VCO wrapper.
2025-05-19 Add CV inputs for cutoff and resonance to ladder filter.
2025-05-19 Adds VCF based on Moog ladder filter

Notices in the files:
README.md:
To support plugins derived from GPL licensed code, some plugins have been licenced using GPL v3.
To encourage third party plugin developement, there is a plugin template released under MIT license.
These files are published under the MIT license, specifically to allow and encourage developers to create new plugins without restricitve licensing constraints.
panels/pcb/10hp_generic/10hp_generic.kicad_pcb:
riban ltd © 2024
